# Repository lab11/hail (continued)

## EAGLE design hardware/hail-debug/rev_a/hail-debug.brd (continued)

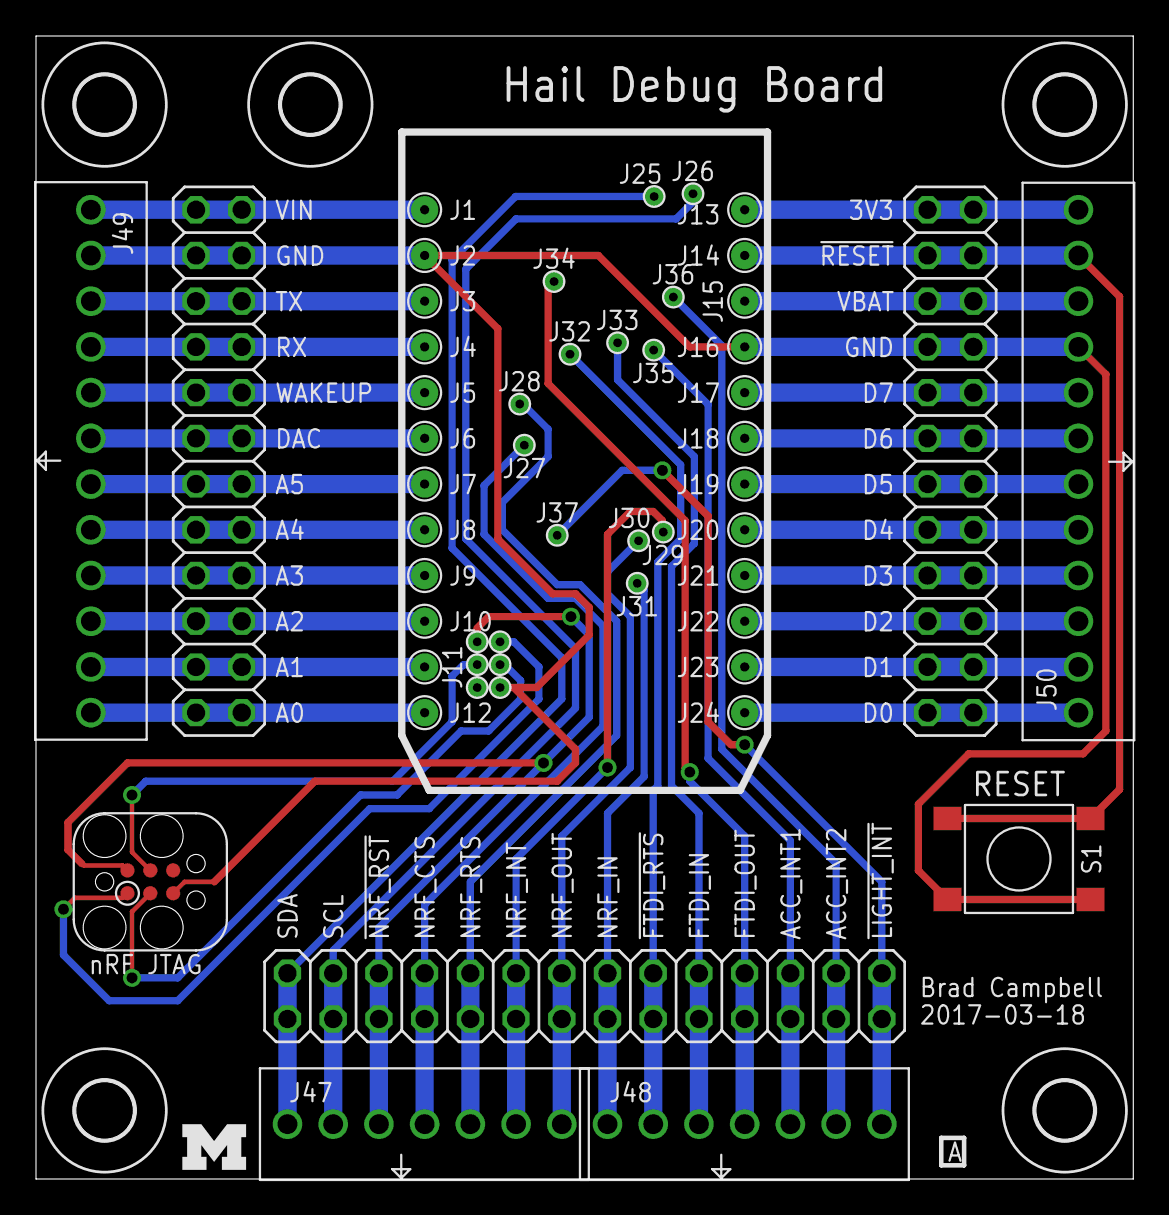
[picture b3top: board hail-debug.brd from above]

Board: 2 copper layers, 61.0 x 63.5 mm, 58 parts (0 on the bottom side), 40 nets.

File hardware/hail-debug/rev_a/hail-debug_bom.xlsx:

Qty | Value | Device | Package | Parts | Description | DIGIKEY | MOUSER | NEWARK
24 | MILLMAX_0908-X-15-20-75-14-11-0 | MILLMAX_0908-X-15-20-75-14-11-0 | POGO_0908-X-15-20-75-14-11-0 | J1, J2, J3, J4, J5, J6, J7, J8, J9, J10, J11, J12, J13, J14, J15, J16, J17, J18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 |  | ED90384-ND
19 | MILLMAX_0985-X-15-20-71-14-11-0 | MILLMAX_0985-X-15-20-71-14-11-0 | POGO_0985-X-15-20-71-14-11-0 | J25, J26, J27, J28, J29, J30, J31, J32, J33, J34, J35, J36, J37, J38, J39, J40,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 |  | ED1122-ND
2 |  | PINHD-2X12 | 2X12 | J44, J45 | PIN HEADER | S2011EC-12-ND
1 |  | PINHD-2X14 | 2X14 | J46 | PIN HEADER | S2011EC-14-ND
2 | SCREW-TERMINAL_7_0.100 | SCREW-TERMINAL_7_0.100 | CONN_BLOCK_7 | J47, J48 | 7x 0.100 in screw terminal block | 277-1278-ND | 651-1725708 | 14X4980
2 | SCREW_TERMINAL_12_0.100 | SCREW_TERMINAL_12_0.100 | CONN_BLOCK_12 | J49, J50 |  | 277-1283-ND
1 | PTS645SM43SMTR92 | PTS645SM43SMTR92 | PTS645 | S1 | Tactile Switch SPST-NO Top Actuated Surface Mount | CKN9112CT-ND

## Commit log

2016-12-03 Renamed to Hail. Added BOM
2016-12-03 Last silkscreen modification
2016-12-03 Panelization of hail
2016-12-03 Ready for fab
2016-12-03 Updates from Brad
2016-12-04 firestorm bootloader
2016-12-04 updating bootloader for hail
2016-12-04 removed more stuff
2016-12-04 updated makefile for bootloader
2016-12-05 Fix bom for github, maybe?
2016-12-05 Update mistaken digikey part numbers
2016-12-05 Fix autogenerated boms
2016-12-05 Last changes to hail_bom
2016-12-14 fix USART3 mistake
2016-12-15 flashes blink!
2016-12-15 refactored and added comments
2016-12-16 command line args
2016-12-16 add miniterm support for listen
2016-12-16 move to class
2016-12-16 updated dtr and rts to new api
2016-12-16 better args
2016-12-16 add readme
2016-12-16 Update to BOM
2016-12-16 Moving hail board to new repo
2016-12-16 Move to hardware directory
2016-12-16 create src/ tree when building bootloader
2016-12-17 add first attempt at labels
2016-12-17 moved tock loader to own repo
2016-12-17 make flash-bootloader
2016-12-17 start on commissioning script
2016-12-17 Added serialization app for the nRF
2016-12-17 Reconfigure hardware folder
    In the future there could be addtional hail hardware
2016-12-17 expanded readme
2016-12-17 Remove debug led blinking
2016-12-17 adding nrf to commission script
2016-12-17 Fix mistaken pin names and BOM parts
    Pins:
    * fix RGB led pins
    * correct mapping of NRF_RTS/CTS pins
    BOM:
    * FB1 was 0603 by mistake. Picked 0402 package
    * Found part for 12-pin headers for Hail
2016-12-17 fixes
2016-12-17 Clarify initial conditions in help message
2016-12-17 Let the nRF set its own BLE address
2016-12-17 Updated PDF to match changes in schematic
2016-12-17 Added many READMEs
    Also renamed nrf_software to nrf-software
2016-12-18 add s130 serialization app for nrf
2016-12-19 disable LEDs on serialization
2016-12-19 actually 0x13
2016-12-19 add note about ftx_prog
2016-12-19 clean up bootloader
    remove a bunch of source files we don't need.
2016-12-19 don't need prepare.py script
2016-12-19 more sane bootloader build
2016-12-19 change to bootloader flash in commission script
2016-12-19 Started on a revision B
2016-12-19 no need for makefile to be executable
2016-12-20 move serialization app to central repo
2016-12-20 Actually create a binary
    Don't just call an elf a bin file
2016-12-20 No changes: dos2unix
2017-01-06 bootloader: fix bug where CRC returned too much
2017-03-04 update to light colored label
2017-03-04 update bom with prices
2017-03-04 add get attr and set attr to the bootloader
2017-03-04 remove old bootloader defines
2017-03-11 bootloader has moved to helena-project/tock-bootloader
2017-03-11 add hail bootloader
2017-03-11 set attribute
2017-03-12 update commission script
    use tockloader!
2017-03-12 flash kernel and app on commission
2017-03-13 Bump tock rev. Loads right kernel and app
2017-03-13 set id attribute
2017-03-13 Unplug USB after running the FTDI step
2017-03-13 creating breakoutboard
2017-03-13 add gitignore
2017-03-13 small fixes
2017-03-13 updates to debug board
2017-03-13 new img
2017-03-13 better color
2017-03-13 Hail rev B!
2017-03-13 Hail revB production files
2017-03-14 add 3d parts
2017-03-17 update layout for MacroFab Standard 4 Layer DRU
2017-03-18 add mpn
    still more to be done here. if you add mpn for house parts you don't get
    the house parts. macrofab is frustratingly difficult to set up. arg.
2017-03-18 finally got the attributes right
2017-03-18 add license
2017-03-18 clean up bom a bit
2017-03-18 update license
2017-03-18 fix images
2017-03-19 ready to ship hail-debug
2017-03-19 add zips
2017-03-19 update commission readme
2017-03-19 use tockloader, not jlink directly
2017-03-19 remove nrf software
2017-03-19 remove nrf software folder
2017-03-19 add buy link
2017-03-19 clean up labels
2017-03-19 add labels readme
2017-03-20 Minor trace tweaks. Bump up size of RF trace
2017-03-20 update bootloader bin
2017-03-21 update 3d parts
2017-03-26 update to new tockloader
2017-03-27 update bin file for bootloader
    now has attributes in it
2017-03-27 dont have to commission base flags
2017-04-24 updated 3d parts for debug board
2017-04-24 newest tock
2017-04-25 newester tock
2017-04-25 more media for hail
2017-04-26 Add pinout/guide
2017-04-26 fix image size
2017-04-26 sigh.. GN -> GND
2017-07-25 update to new commission point
2017-07-27 fix commission
    update old commands
2017-07-27 Add pinout diagram here too
2017-08-01 add flier
2017-09-19 Updated to head of tock
2017-09-26 Revision C of Hail
    Closes #1
2017-09-26 Build files for rev c
2017-10-25 Update tock to newest master
2017-10-25 commissioning: add libftdi-dev pre-req
2017-10-25 commissioning: add troubleshooting
2017-10-25 Explain svg_utils installation
2017-10-25 Update labels for our new printer
2017-10-25 Testing instructions
2017-12-07 allow skipping ftdi on mac
2018-01-17 Updated Hail cards
2018-08-08 first pass on hail-wifi board
2018-12-02 some updates to hail-wifi
    Rev a doesn't work (wrong esp chip), but I hacked a version which I hope
    will work and then I will make a rev b.
2018-12-02 .gitignore
2018-12-02 add tock board for hail-wifi
2018-12-10 checkpoint
    actually do have esp32 connecting to wifi and doing http requests
